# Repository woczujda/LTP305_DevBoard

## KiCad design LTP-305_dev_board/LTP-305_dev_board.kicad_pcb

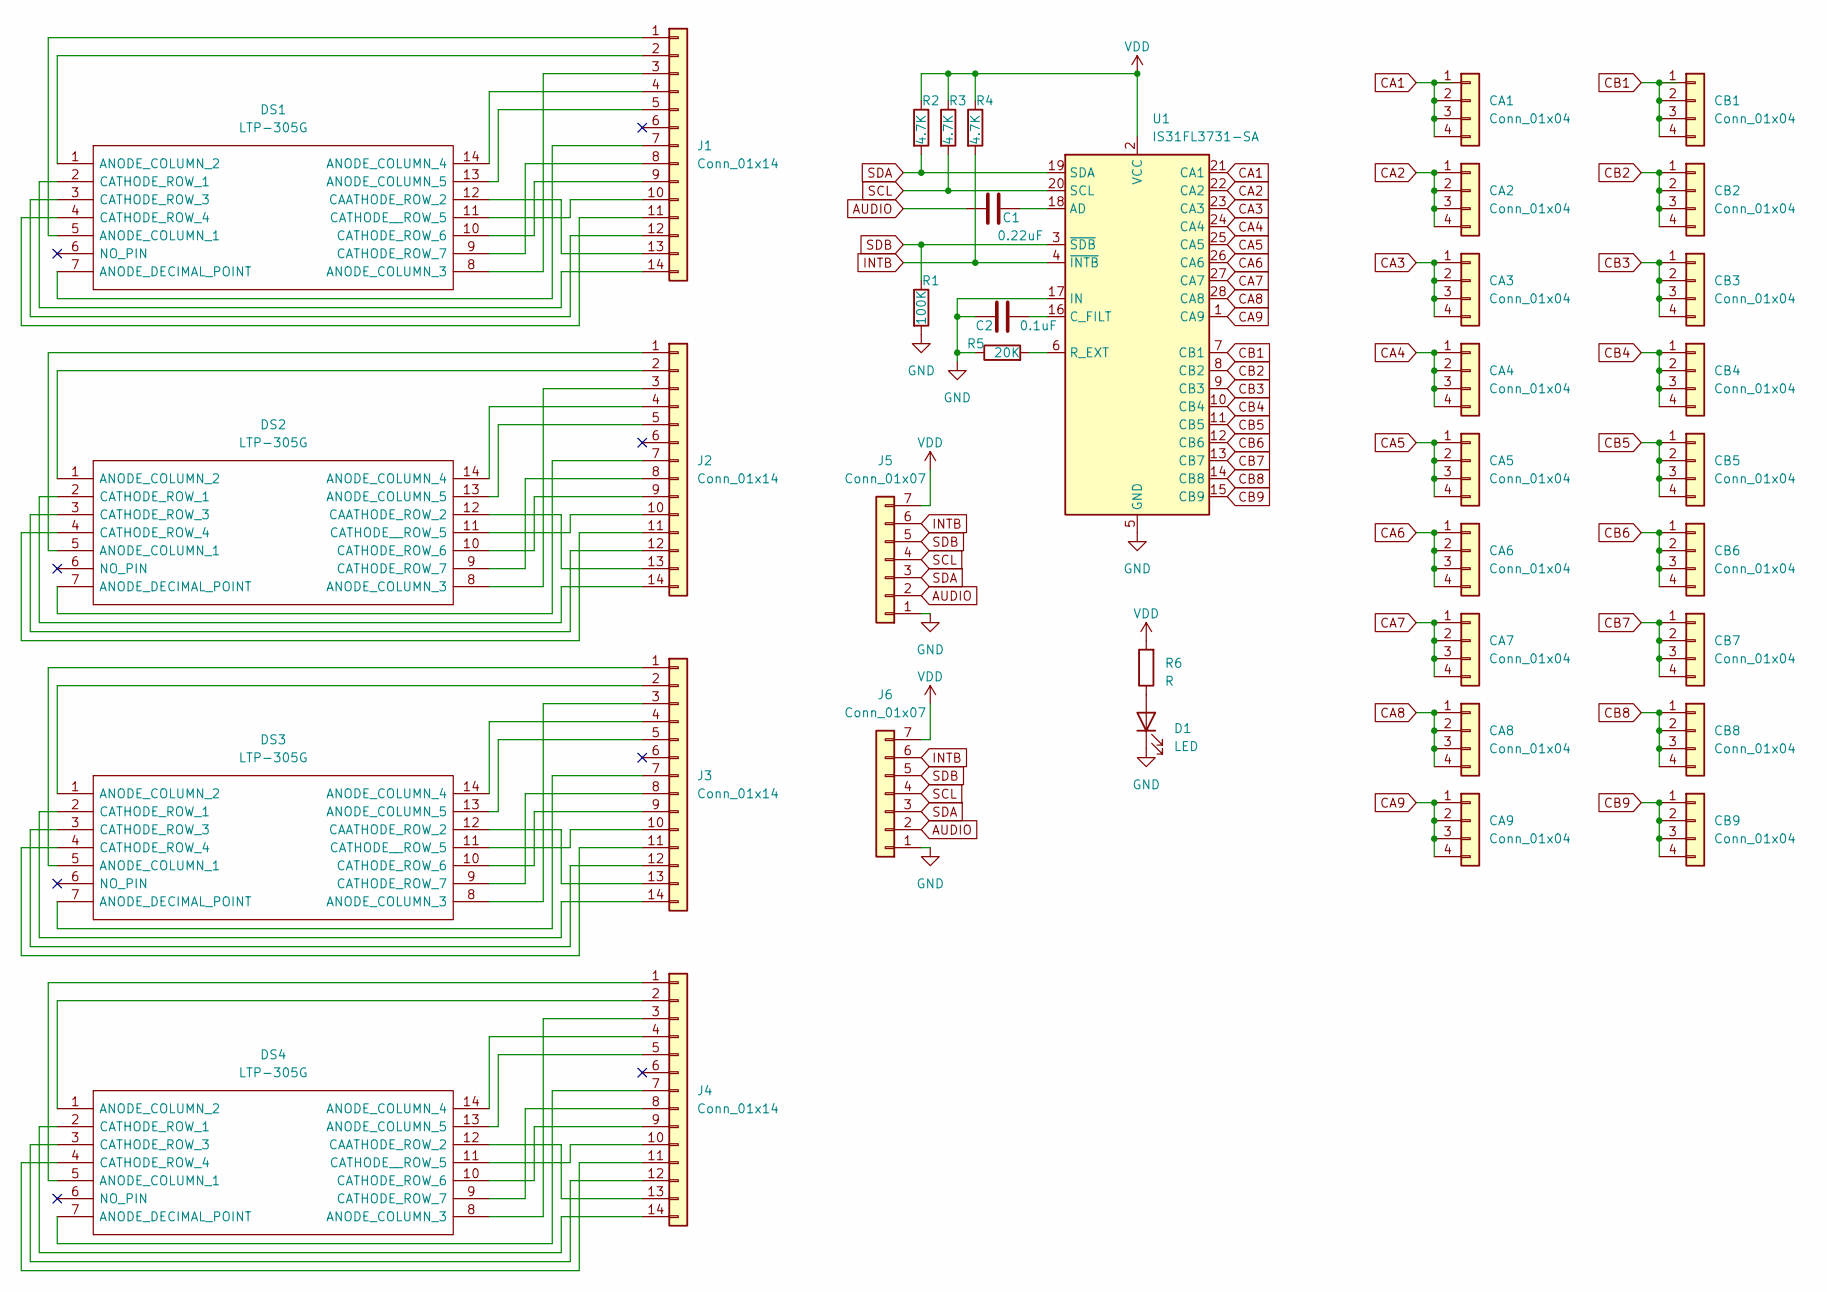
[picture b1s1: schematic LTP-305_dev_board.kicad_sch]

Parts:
C1: 0.22uF; R_0603_1608Metric_Pad0.98x0.95mm_HandSolder
C2: 0.1uF; R_0603_1608Metric_Pad0.98x0.95mm_HandSolder
CA1, CA2, CA3, CA4, CA5, CA6, CA7, CA8, CA9: Conn_01x04; PinHeader_1x04_P1.27mm_Vertical
CB1, CB2, CB3, CB4, CB5, CB6, CB7, CB8, CB9: Conn_01x04; PinHeader_1x04_P1.27mm_Vertical
D1: LED; LED_0603_1608Metric_Pad1.05x0.95mm_HandSolder
DS1, DS2, DS3, DS4: LTP-305G; DIPS762W50P254L1850H400Q14N; Mouser Part Number 859-LTP-305G
J1, J2, J3, J4: Conn_01x14; PinHeader_2x07_P1.27mm_Vertical
J5: Conn_01x07; PinHeader_1x07_P2.54mm_Vertical
J6: Conn_01x07; Pin_jumper_1x7_P2.54mm
R1: 100K; R_0603_1608Metric_Pad0.98x0.95mm_HandSolder
R2, R3, R4: 4.7K; R_0603_1608Metric_Pad0.98x0.95mm_HandSolder
R5: 20K; R_0603_1608Metric_Pad0.98x0.95mm_HandSolder
R6: R; R_0603_1608Metric_Pad0.98x0.95mm_HandSolder
U1: IS31FL3731-SA; QFN-28-1EP_4x4mm_P0.4mm_EP2.3x2.3mm

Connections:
AUDIO: C1.2, J5.2, J6.2
CA1: CA1.1, CA1.2, CA1.3, CA1.4, U1.21 (CA1)
CA2: CA2.1, CA2.2, CA2.3, CA2.4, U1.22 (CA2)
CA3: CA3.1, CA3.2, CA3.3, CA3.4, U1.23 (CA3)
CA4: CA4.1, CA4.2, CA4.3, CA4.4, U1.24 (CA4)
CA5: CA5.1, CA5.2, CA5.3, CA5.4, U1.25 (CA5)
CA6: CA6.1, CA6.2, CA6.3, CA6.4, U1.26 (CA6)
CA7: CA7.1, CA7.2, CA7.3, CA7.4, U1.27 (CA7)
CA8: CA8.1, CA8.2, CA8.3, CA8.4, U1.28 (CA8)
CA9: CA9.1, CA9.2, CA9.3, CA9.4, U1.1 (CA9)
CB1: CB1.1, CB1.2, CB1.3, CB1.4, U1.7 (CB1)
CB2: CB2.1, CB2.2, CB2.3, CB2.4, U1.8 (CB2)
CB3: CB3.1, CB3.2, CB3.3, CB3.4, U1.9 (CB3)
CB4: CB4.1, CB4.2, CB4.3, CB4.4, U1.10 (CB4)
CB5: CB5.1, CB5.2, CB5.3, CB5.4, U1.11 (CB5)
CB6: CB6.1, CB6.2, CB6.3, CB6.4, U1.12 (CB6)
CB7: CB7.1, CB7.2, CB7.3, CB7.4, U1.13 (CB7)
CB8: CB8.1, CB8.2, CB8.3, CB8.4, U1.14 (CB8)
CB9: CB9.1, CB9.2, CB9.3, CB9.4, U1.15 (CB9)
GND: C2.2, D1.1 (K), J5.1, J6.1, R1.2, R5.1, U1.5 (GND), U1.17 (IN), U1.29 (GND)
INTB: J5.6, J6.6, R4.2, U1.4 (~INTB)
unnamed: C1.1, U1.18 (AD)
unnamed: C2.1, U1.16 (C_FILT)
unnamed: DS1.1 (ANODE_COLUMN_2), J1.2
unnamed: DS1.2 (CATHODE_ROW_1), J1.14
unnamed: DS1.3 (CATHODE_ROW_3), J1.12
unnamed: DS1.4 (CATHODE_ROW_4), J1.11
unnamed: DS1.5 (ANODE_COLUMN_1), J1.1
unnamed: DS1.7 (ANODE_DECIMAL_POINT), J1.7
unnamed: DS1.8 (ANODE_COLUMN_3), J1.3
unnamed: DS1.9 (CATHODE_ROW_7), J1.8
unnamed: DS1.10 (CATHODE_ROW_6), J1.9
unnamed: DS1.11 (CATHODE__ROW_5), J1.10
unnamed: DS1.12 (CAATHODE_ROW_2), J1.13
unnamed: DS1.13 (ANODE_COLUMN_5), J1.5
unnamed: DS1.14 (ANODE_COLUMN_4), J1.4
unnamed: DS2.1 (ANODE_COLUMN_2), J2.2
unnamed: DS2.2 (CATHODE_ROW_1), J2.14
unnamed: DS2.3 (CATHODE_ROW_3), J2.12
unnamed: DS2.4 (CATHODE_ROW_4), J2.11
unnamed: DS2.5 (ANODE_COLUMN_1), J2.1
unnamed: DS2.7 (ANODE_DECIMAL_POINT), J2.7
unnamed: DS2.8 (ANODE_COLUMN_3), J2.3
unnamed: DS2.9 (CATHODE_ROW_7), J2.8
unnamed: DS2.10 (CATHODE_ROW_6), J2.9
unnamed: DS2.11 (CATHODE__ROW_5), J2.10
unnamed: DS2.12 (CAATHODE_ROW_2), J2.13
unnamed: DS2.13 (ANODE_COLUMN_5), J2.5
unnamed: DS2.14 (ANODE_COLUMN_4), J2.4
unnamed: DS3.1 (ANODE_COLUMN_2), J3.2
unnamed: DS3.2 (CATHODE_ROW_1), J3.14
unnamed: DS3.3 (CATHODE_ROW_3), J3.12
unnamed: DS3.4 (CATHODE_ROW_4), J3.11
unnamed: DS3.5 (ANODE_COLUMN_1), J3.1
unnamed: DS3.7 (ANODE_DECIMAL_POINT), J3.7
unnamed: DS3.8 (ANODE_COLUMN_3), J3.3
unnamed: DS3.9 (CATHODE_ROW_7), J3.8
unnamed: DS3.10 (CATHODE_ROW_6), J3.9
unnamed: DS3.11 (CATHODE__ROW_5), J3.10
unnamed: DS3.12 (CAATHODE_ROW_2), J3.13
unnamed: DS3.13 (ANODE_COLUMN_5), J3.5
unnamed: DS3.14 (ANODE_COLUMN_4), J3.4
unnamed: DS4.1 (ANODE_COLUMN_2), J4.2
unnamed: DS4.2 (CATHODE_ROW_1), J4.14
unnamed: DS4.3 (CATHODE_ROW_3), J4.12
unnamed: DS4.4 (CATHODE_ROW_4), J4.11
unnamed: DS4.5 (ANODE_COLUMN_1), J4.1
unnamed: DS4.7 (ANODE_DECIMAL_POINT), J4.7
unnamed: DS4.8 (ANODE_COLUMN_3), J4.3
unnamed: DS4.9 (CATHODE_ROW_7), J4.8
unnamed: DS4.10 (CATHODE_ROW_6), J4.9
unnamed: DS4.11 (CATHODE__ROW_5), J4.10
unnamed: DS4.12 (CAATHODE_ROW_2), J4.13
unnamed: DS4.13 (ANODE_COLUMN_5), J4.5
unnamed: DS4.14 (ANODE_COLUMN_4), J4.4
unnamed: R5.2, U1.6 (R_EXT)
SCL: J5.4, J6.4, R3.2, U1.20 (SCL)
SDA: J5.3, J6.3, R2.2, U1.19 (SDA)
SDB: J5.5, J6.5, R1.1, U1.3 (~SDB)

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
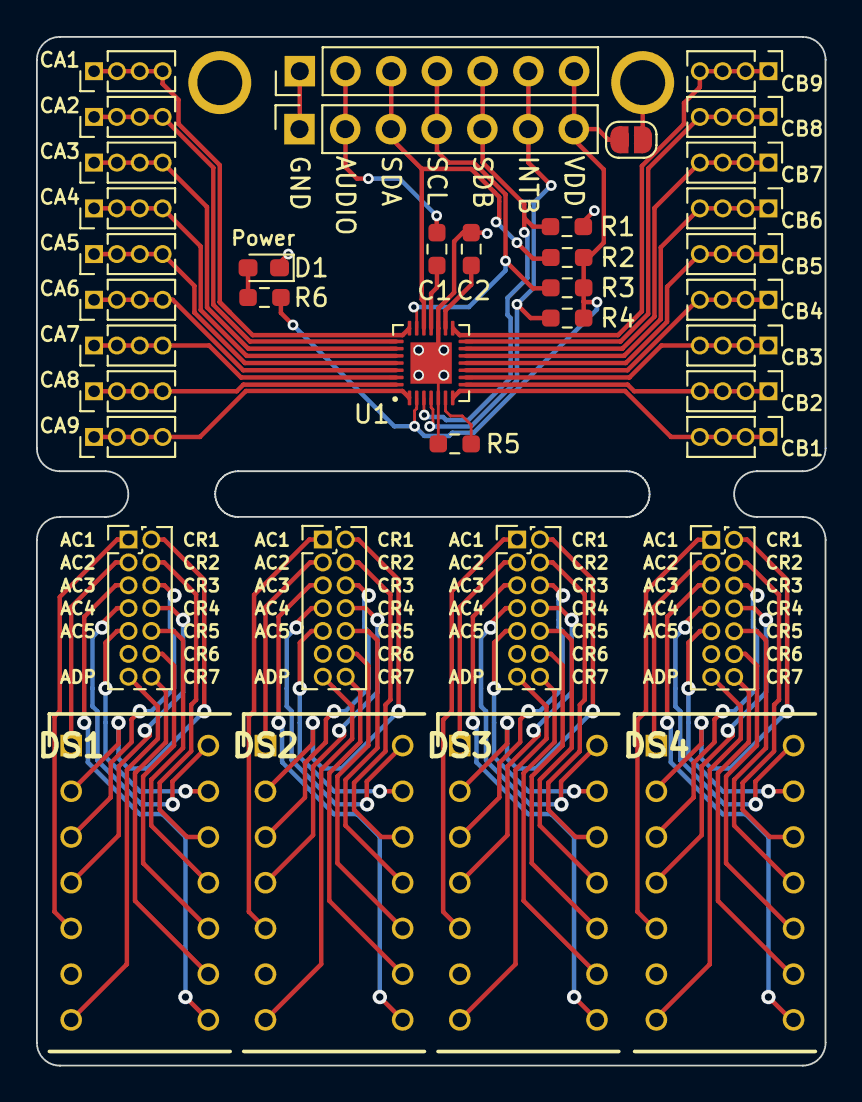
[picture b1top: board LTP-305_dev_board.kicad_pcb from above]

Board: 2 copper layers, 43.8 x 57.1 mm, 38 parts (0 on the bottom side), 81 nets.

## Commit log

2023-01-31 Initial upload
2023-01-31 Changes in schematics and PCB layout
    Added power control LED
    Finished schematics
    New PCB layout
2023-01-31 Board layout update
2023-01-31 rev 0.1 done
2023-02-03 Minor changes
2023-03-13 Changes in board layout
